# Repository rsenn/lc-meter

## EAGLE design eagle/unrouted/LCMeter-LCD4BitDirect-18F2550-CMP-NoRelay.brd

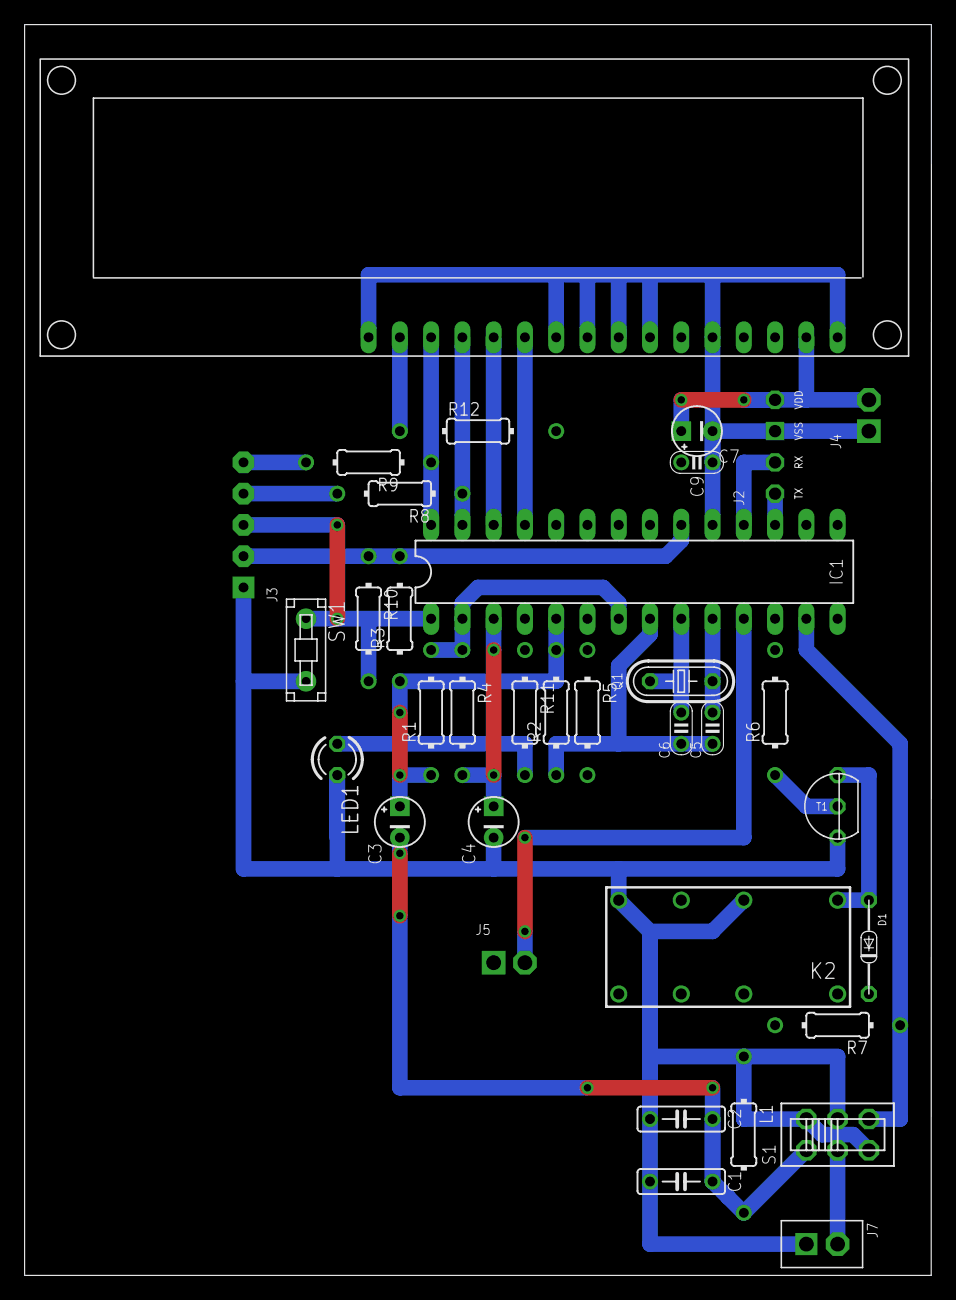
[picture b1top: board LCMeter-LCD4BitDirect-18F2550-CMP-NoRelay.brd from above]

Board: 2 copper layers, 73.7 x 101.6 mm, 35 parts (0 on the bottom side), 31 nets.

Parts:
C1, C2: 1nF; C050-025X060
C3, C4: 10μF; E2,5-4
C5, C6: 15pF; C025-020X036
C7: 100μF; E2,5-4
C9: 100nF; C025-020X036/V
D1: 1N4148; DO34-7
IC1: PIC18F2550-I/SP-COMP-B-V; DIL28-3/V
J2: PIC-UART
J3: PIC-ICSP
J4: PWR; CONN-2P
J5: FREQ; CONN-2P
J7: TEST-LC; CONN-2P-V
K2: DS2Y
L1: 82μH; 0204/12
LCD: HD44780LM016L; LM016L-HD44780
LED1: TLLG4400; LED3MM
Q1: 20MHz; HC49
R1, R2, R3: 100k; 0204/10
R4: 47k; 0204/10-V
R5, R10: 4.7k; 0204/10
R6, R7: 10k; 0204/10-V
R8, R9: 100; 0204/10-V
R11: 1k; 0204/10-V
R12: 330; 0204/12
S1: SL-SW-2P-2T; SLSW-2P2T
SW1: PB-1P-1T; PB-1P1T
T1: 2N3904; TO92

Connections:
/LC: IC1.13, R7.2, S1.6
/MCLR: IC1.1, J3.3, R10.2, SW1.2
/RELAY: IC1.12, R6.1
/RX: IC1.18, J2.18
/TX: IC1.17, J2.17
A0: IC1.2, IC1.7, R1.2, R4.2
A1: C4.+, IC1.3, R4.1
A3: C3.+, IC1.5, R1.1, R2.2, R3.1
A4: IC1.6, R5.1
C2_CON: C2.2, K2.4
D4: IC1.25, LCD.11
D5: IC1.26, LCD.12
D6: IC1.27, LCD.13, R8.2
D7: IC1.28, LCD.14, R9.2
E: IC1.24, LCD.6
FREQ: IC1.11, J5.2
GND: C1.2, C4.-, C5.1, C6.1, C7.-, C9.1, IC1.8, IC1.19, J2.19, J3.1, J4.1, J5.1, J7.1, K2.8, LCD.1, LCD.5, LCD.7, LCD.8, LCD.9, LCD.10, LCD.16, LED1.K, R2.1, S1.5, SW1.1, T1.1
IN+: J7.2, S1.2
unnamed: LED1.A, R11.1
unnamed: C1.1, C2.1, C3.-, L1.2, S1.1
unnamed: IC1.4, R11.2
unnamed: LCD.15, R12.1
unnamed: R6.2, T1.2
unnamed: L1.1, S1.3, S1.4
unnamed: D1.A, K2.1, T1.3
OSC1: C6.2, IC1.9, Q1.2
OSC2: C5.2, IC1.10, Q1.1
PGC: J3.4, R8.1
PGD: J3.5, R9.1
RS: IC1.23, LCD.4
VCC: C7.+, C9.2, D1.C, IC1.20, J2.20, J3.2, J4.2, K2.16, LCD.2, R3.2, R5.2, R7.1, R10.1, R12.2

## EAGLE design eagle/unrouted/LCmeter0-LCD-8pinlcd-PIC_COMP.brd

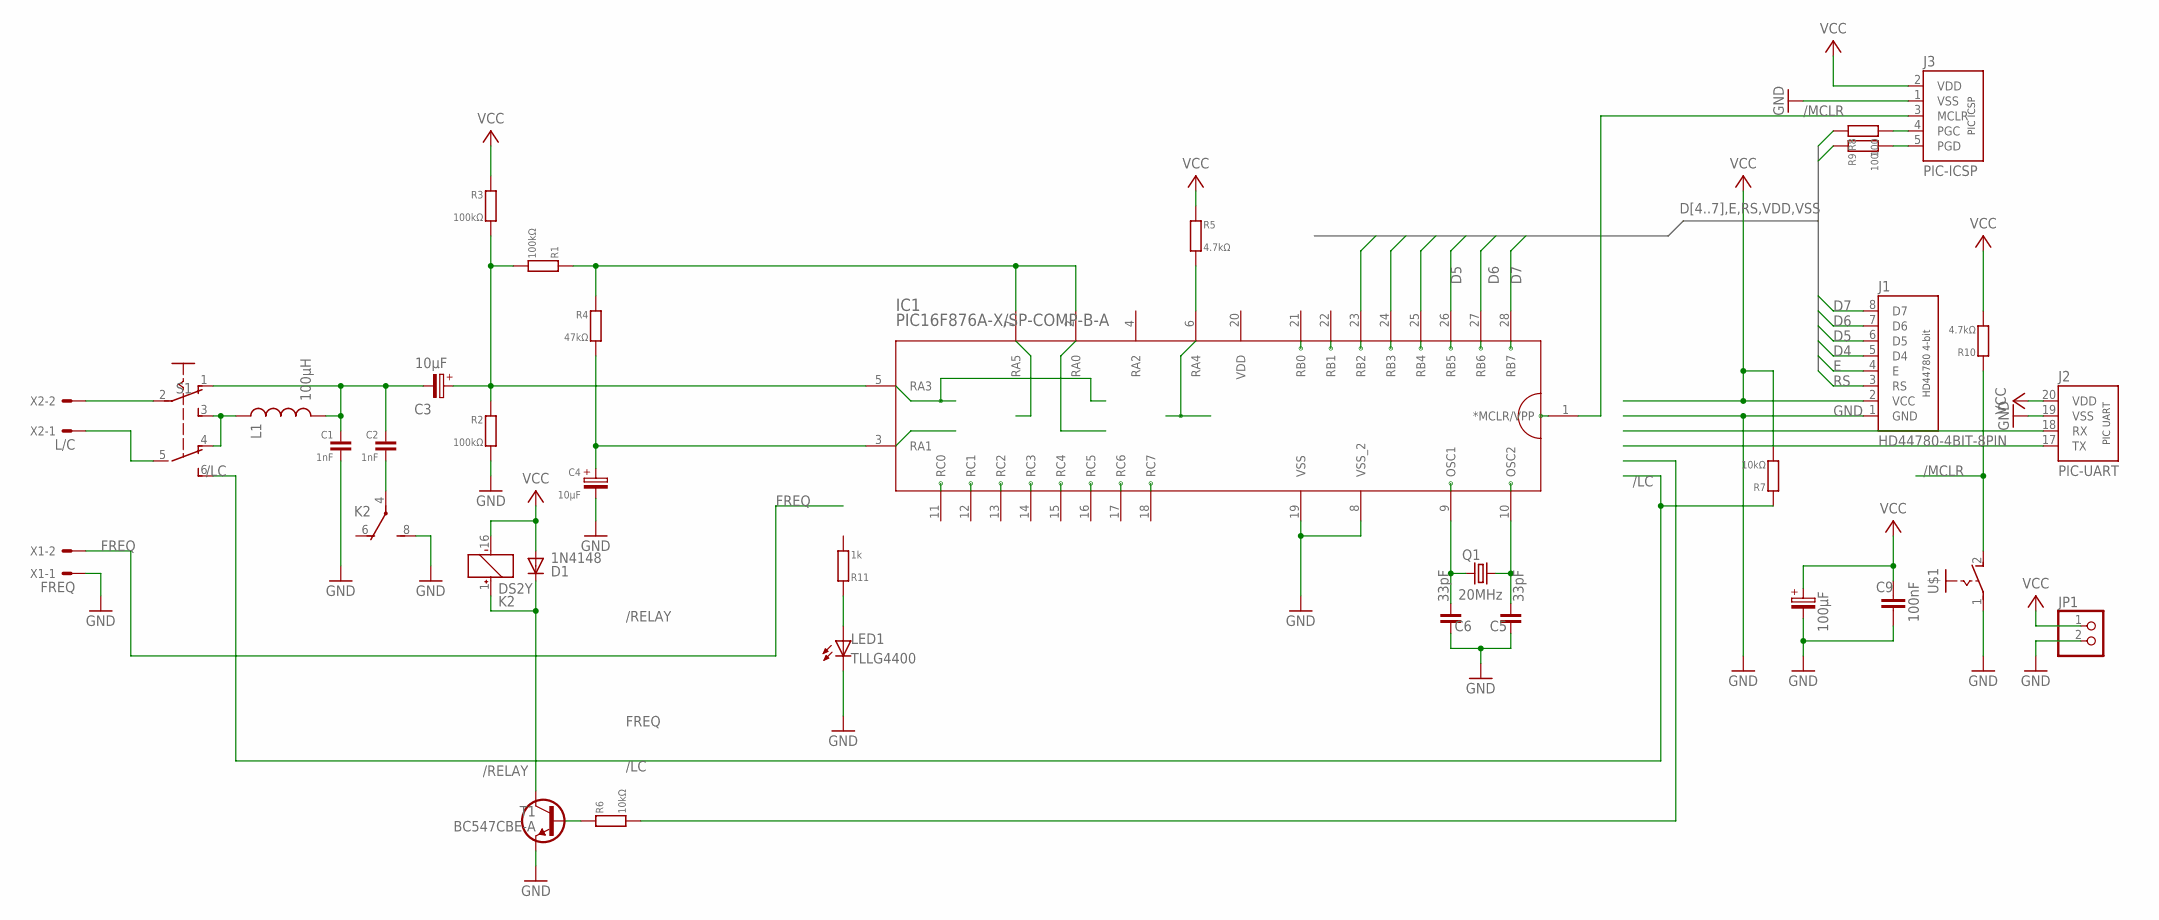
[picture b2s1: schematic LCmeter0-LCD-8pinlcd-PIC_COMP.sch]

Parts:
C1, C2: 1nF; C050-020X036
C3, C4: 10μF; E2,5-4
C5, C6: 33pF; C025-020X036
C7: 100μF; E2,5-6
C9: 100nF; C025-024X044
D1: 1N4148; DO34-7
IC1: PIC16F876A-X/SP-COMP-B-A; DIL28-3
J1: HD44780-4BIT-8PIN; CONN-8P
J2: PIC-UART
J3: PIC-ICSP; CONN-5P
JP1: PINHD-1X2; 1X02
K2: DS2Y
L1: 100μH; L-02/5
LED1: TLLG4400; LED3MM
Q1: 20MHz; HC49
R1, R2, R3: 100kΩ; 0202/7
R4: 47kΩ; 0202/7
R5, R10: 4.7kΩ; 0202/7
R6: 10kΩ; 0202/7
R7: 10kΩ; 0202/10
R8, R9: 100; 0202/5
R11: 1k; 0202/5
S1: SL-SW-2P-2T; SLSW-2P2T
T1: BC547CBE-A; TO92-CBE-A
U$1: PB-1P-1T; PB-1P1T
X1: FREQ; 70543-02
X2: L/C; 70543-02

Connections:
/LC: R7.1, S1.6 (S1)
/MCLR: IC1.1 (*MCLR/VPP), J3.3 (MCLR), R10.1, U$1.2 (S)
/RELAY: D1.C, K2.1 (+), T1.C
A0: IC1.2 (RA0), IC1.7 (RA5), R1.1, R4.1
A1: C4.+, IC1.3 (RA1), R4.2
A3: C3.+, IC1.5 (RA3), R1.2, R2.1, R3.2
A4: IC1.6 (RA4), R5.2
C2_CON: C2.2, K2.4
D4: IC1.25 (RB4), J1.5 (D4)
D5: IC1.26 (RB5), J1.6 (D5)
D6: IC1.27 (RB6), J1.7 (D6), R9.1
D7: IC1.28 (RB7), J1.8 (D7), R8.1
E: IC1.24 (RB3), J1.4 (E)
FREQ: X1.2
GND: C1.2, C4.-, C5.1, C6.1, C7.-, C9.2, IC1.8 (VSS_2), IC1.19 (VSS), J1.1 (GND), J2.19 (VSS), J3.1 (VSS), JP1.2, K2.8 (S), LED1.K (C), R2.2, T1.E, U$1.1, X1.1
M+: S1.2, X2.2
M-: S1.5 (P1), X2.1
unnamed: J3.4 (PGC), R8.2
unnamed: C1.1, C2.1, C3.-, L1.2, S1.1 (O)
unnamed: J3.5 (PGD), R9.2
unnamed: R6.1, T1.B
unnamed: LED1.A, R11.1
unnamed: L1.1, S1.3 (S), S1.4 (O1)
OSC1: C6.2, IC1.9 (OSC1), Q1.1
OSC2: C5.2, IC1.10 (OSC2), Q1.2
RC5: R6.2
RS: IC1.23 (RB2), J1.3 (RS)
RX: J2.18 (RX)
VCC: C7.+, C9.1, D1.A, J1.2 (VCC), J2.20 (VDD), J3.2 (VDD), JP1.1, K2.16 (-), R3.1, R5.1, R7.2, R10.2

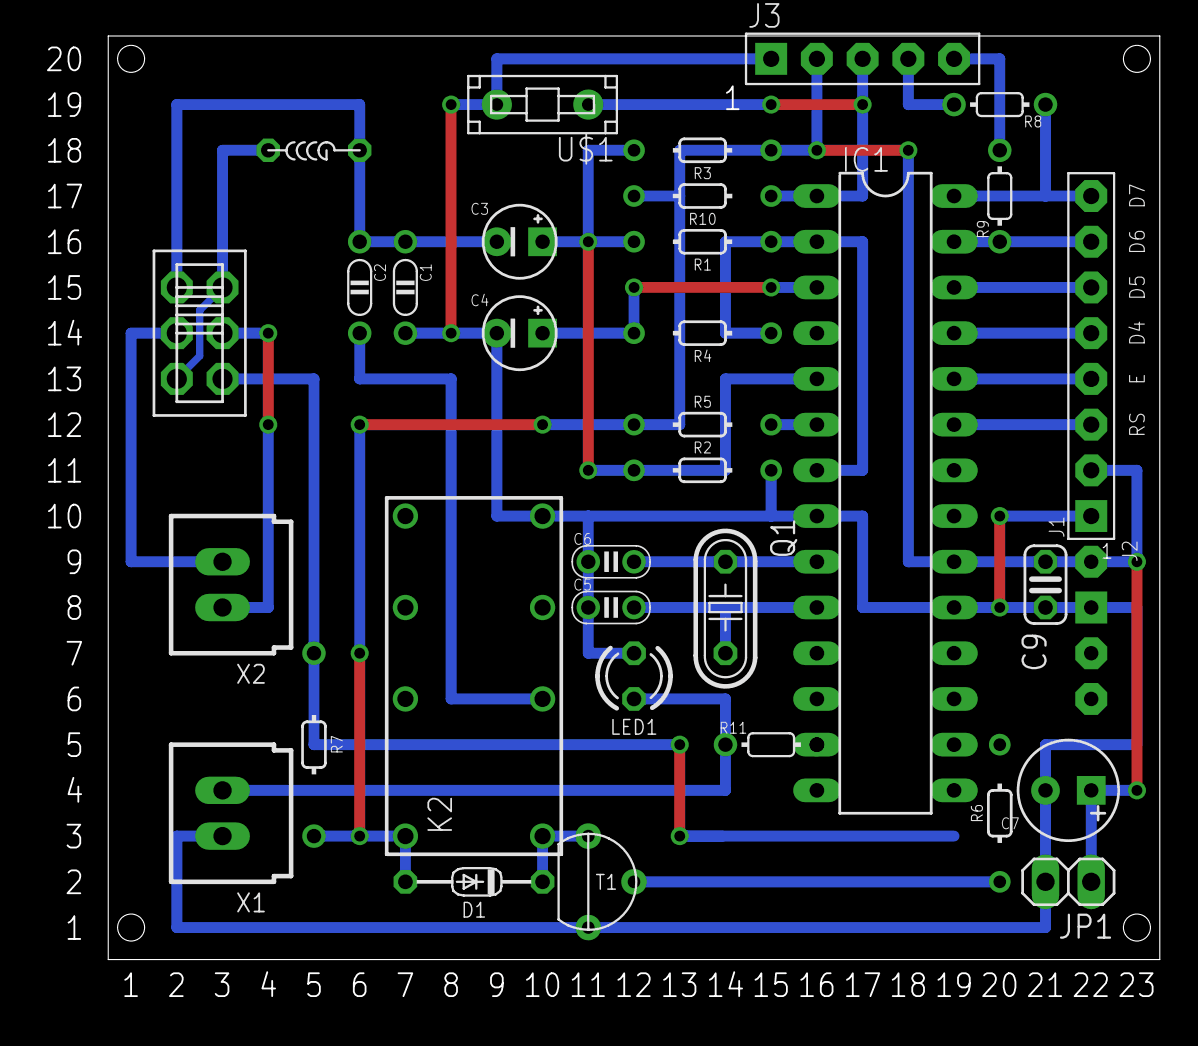
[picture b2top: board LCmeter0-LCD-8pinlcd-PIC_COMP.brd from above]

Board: 2 copper layers, 58.4 x 51.3 mm, 34 parts (0 on the bottom side), 26 nets.

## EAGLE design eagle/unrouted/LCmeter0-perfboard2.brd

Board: 2 copper layers, 25 parts (0 on the bottom side), 22 nets.

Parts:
C1, C2: 1nF; C050-024X044
C3, C4: 10μF; E5-4
C5, C6: 33pF; C050-024X044
C7: 100μF; E2,5-6
C8: 10μF; E2,5-5
C9: 100nF; C025-024X044
D1: 1N4148; DO35-7
IC1: PIC16F876A-X/SP; DIL28-3
K2: DS2Y
L1: 100μH; 0204/5
LCD1: HD44780; MA08-1
Q1: 20MHz; HC49/S
Q2: BC548; TO92-EBC
R1: 100kΩ; 0204/7
R2, R3: 100kΩ; 0204V
R4: 47kΩ; 0204V
R5: 4.7kΩ; 0204/7
R6: 10kΩ; 0207/10
R10: 4.7kΩ; 0207/10
SW1: SPST; PB-5
SW2: DPDT

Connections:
/LC: IC1.15, SW2.2-3
/MCLR: IC1.1, R10.1, SW1.3
/RELAY: D1.C, K2.1, Q2.C
A0: IC1.2, IC1.7, R1.2, R4.2
A1: C4.+, IC1.3, R4.1
A3: C3.+, IC1.5, R1.1, R2.2, R3.1
A4: IC1.6, R5.1
C2_CON: C2.2, K2.4
D4: IC1.25, LCD1.5
D5: IC1.26, LCD1.6
D6: IC1.27, LCD1.7
D7: IC1.28, LCD1.8
E: IC1.24, LCD1.4
GND: C1.2, C4.-, C5.1, C6.1, C7.-, C8.-, C9.2, IC1.8, IC1.19, K2.8, LCD1.1, Q2.E, R2.1, SW1.1
unnamed: C1.1, C2.1, C3.-, L1.2, SW2.1-2
unnamed: Q2.B, R6.2
unnamed: L1.1, SW2.1-3, SW2.2-2
OSC1: C6.2, IC1.9, Q1.1
OSC2: C5.2, IC1.10, Q1.2
RC5: IC1.16, R6.1
RS: IC1.23, LCD1.3
VCC: C7.+, C8.+, C9.1, D1.A, IC1.20, K2.16, LCD1.2, R3.2, R5.2, R10.2
